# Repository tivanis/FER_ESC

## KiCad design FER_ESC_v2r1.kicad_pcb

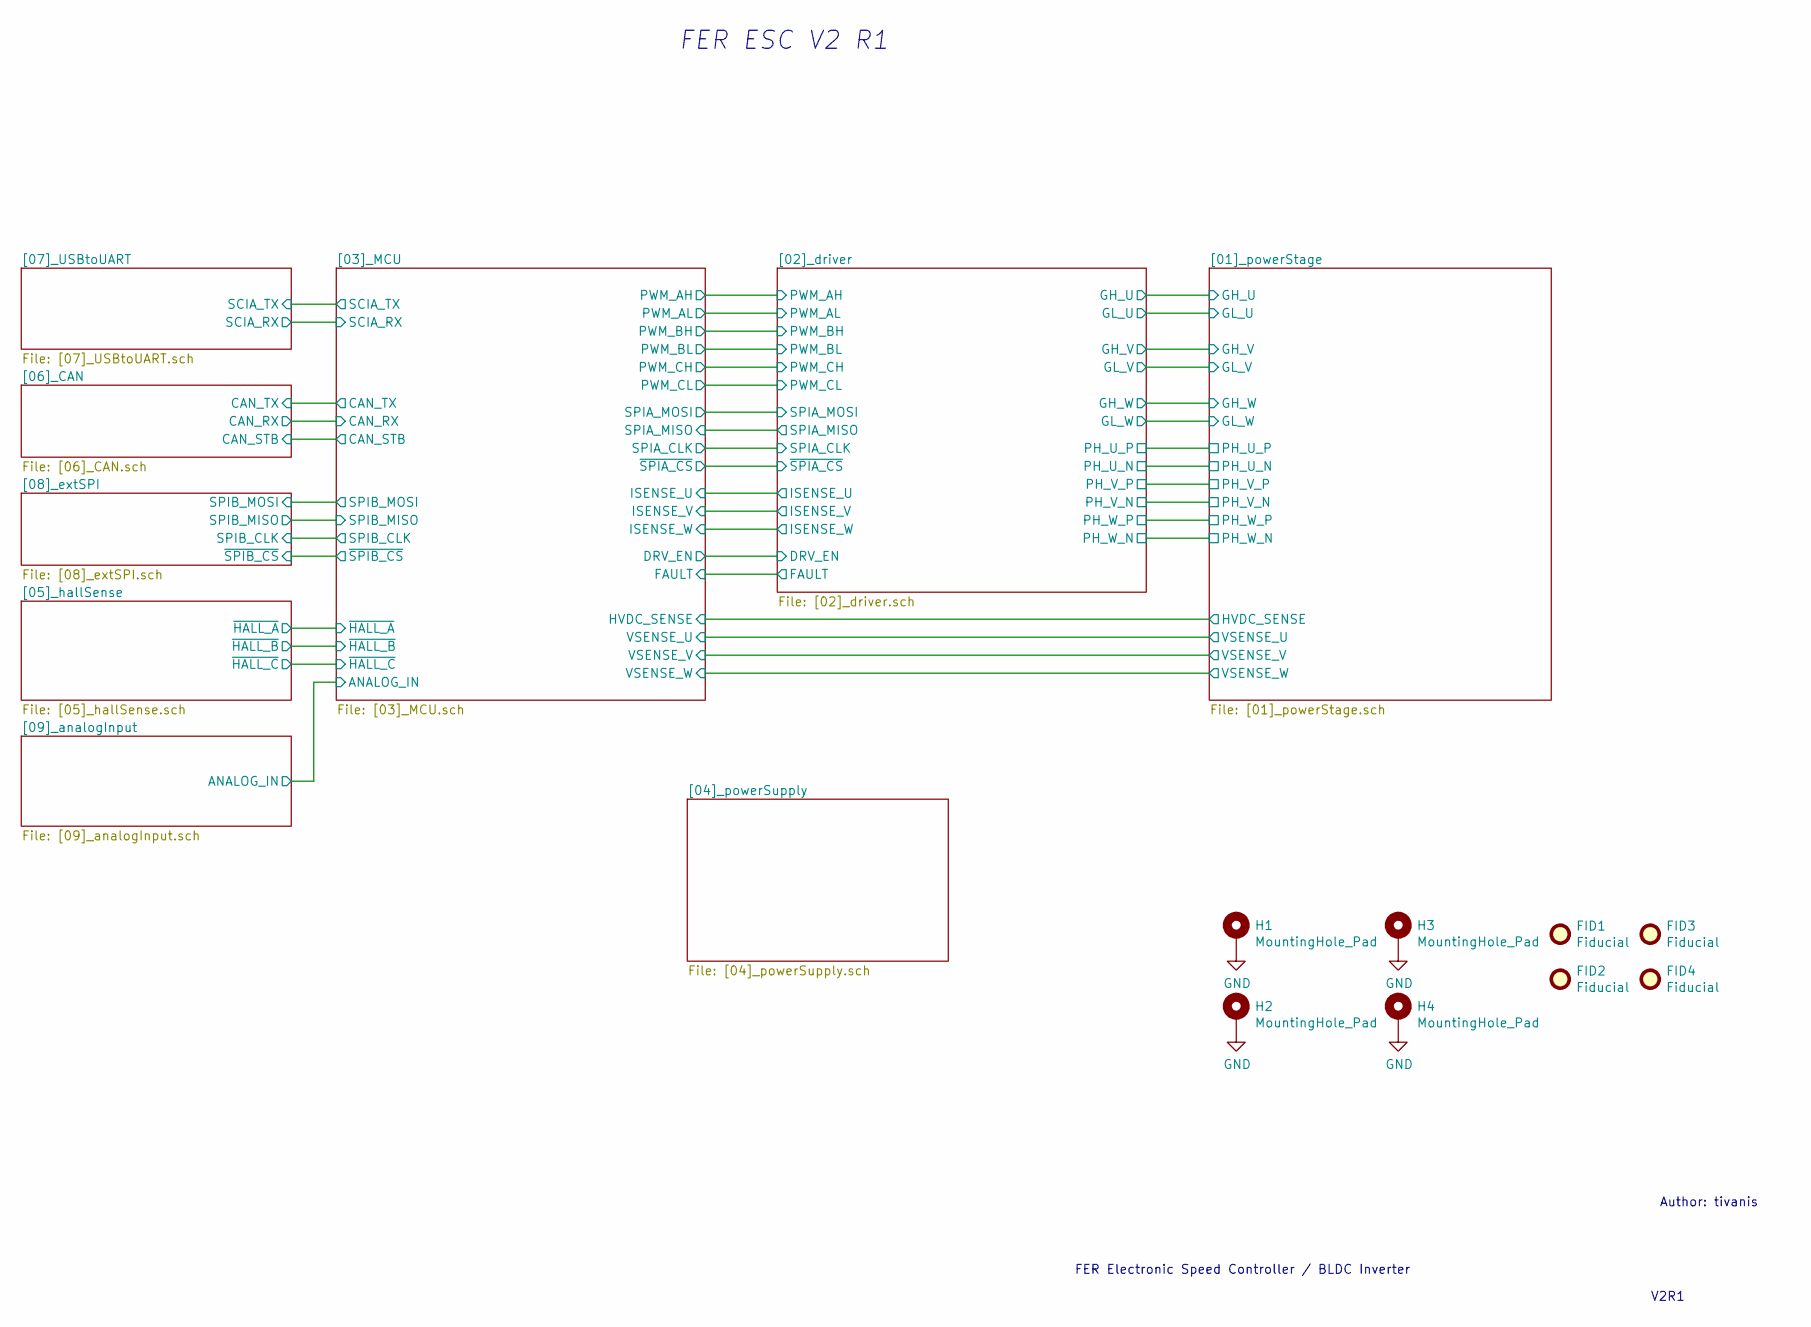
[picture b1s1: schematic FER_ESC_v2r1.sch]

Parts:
FID1, FID2, FID3, FID4: Fiducial; Fiducial_0.5mm_Mask1.5mm
H1, H2, H3, H4: MountingHole_Pad; MountingHole_3.2mm_M3_DIN965_Pad

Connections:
GND: H1.1, H2.1, H3.1, H4.1; also elsewhere on the board

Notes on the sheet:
FER ESC V2 R1
V2R1
FER Electronic Speed Controller / BLDC Inverter
Author: tivanis

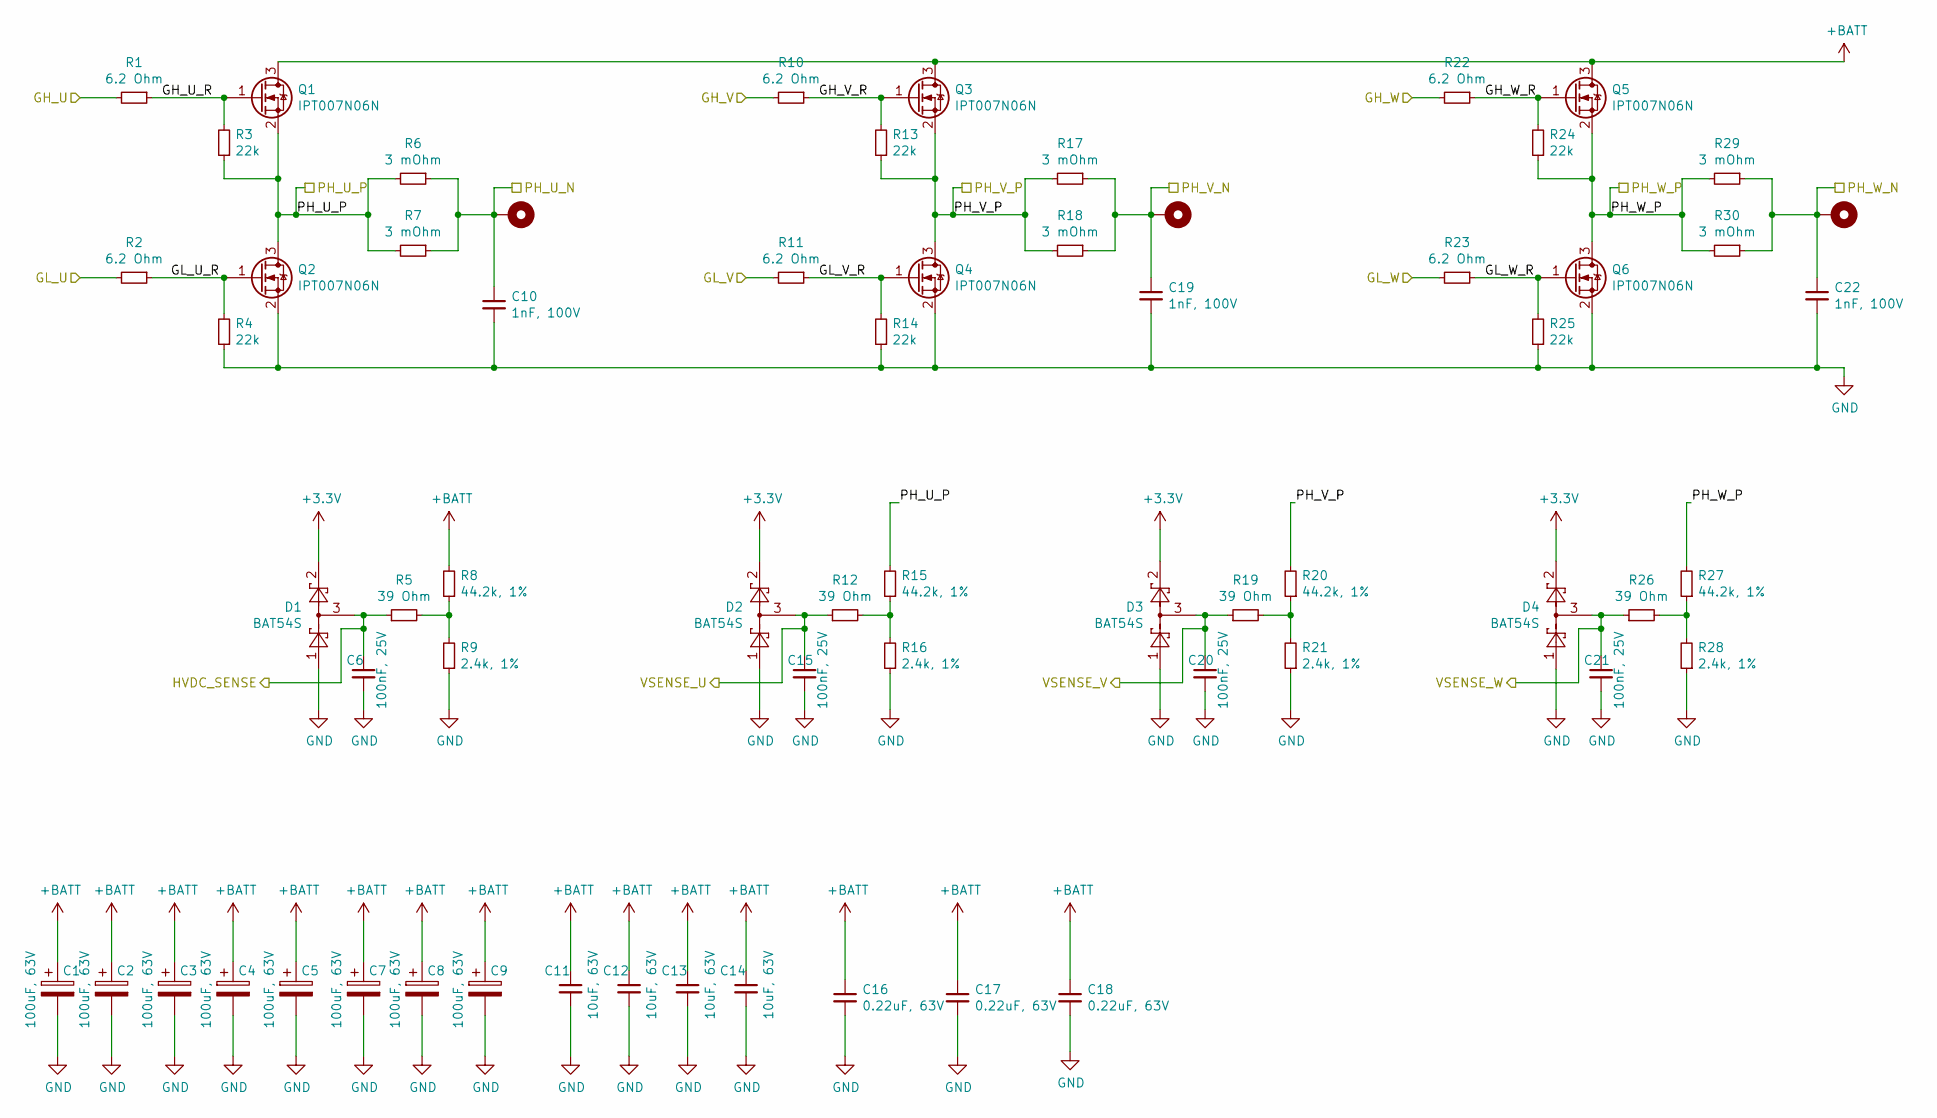
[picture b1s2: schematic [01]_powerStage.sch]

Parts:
C1, C2, C3, C4, C5, C7, C8, C9: 100uF, 63V; CP_Elec_10x14.3; Manufacturer Part Number EEH-ZS1J151V
C6, C15, C20, C21: 100nF, 25V; C_0603_1608Metric; Manufacturer Part Number C0603C104Z3VACTU
C10, C19, C22: 1nF, 100V; C_0603_1608Metric; Manufacturer Part Number C0603C102K1RACTU
C11, C12, C13, C14: 10uF, 63V; C_1210_3225Metric; Manufacturer Part Number CL32B106KMVNNWE
C16, C17, C18: 0.22uF, 63V; C_1206_3216Metric; Manufacturer Part Number C1206C224MMRECTU
D1, D2, D3, D4: BAT54S; SOT-23; Manufacturer Part Number BAT54S-TP
H5, H6, H7: MountingHole_Pad; MountingHole_4mm_Pad_Via
Q1, Q2, Q3, Q4, Q5, Q6: IPT007N06N; Infineon_PG-HSOF-8-1_ThermalVias; Manufacturer Part Number NVBLS001N06C
R1, R2, R10, R11, R22, R23: 6.2 Ohm; R_0805_2012Metric; Manufacturer Part Number ERJ-P06J6R2V
R3, R4, R13, R14, R24, R25: 22k; R_0805_2012Metric; Manufacturer Part Number ERJ-PA3J223V
R5, R12, R19, R26: 39 Ohm; R_0603_1608Metric; Manufacturer Part Number CR0603-FX-39R0ELF
R6, R7, R17, R18, R29, R30: 3 mOhm; R_2512_6332Metric; Manufacturer Part Number CSS2H-2512K-3L00FE
R8, R15, R20, R27: 44.2k, 1%; R_0603_1608Metric; Manufacturer Part Number CR0603-FX-4422ELF
R9, R16, R21, R28: 2.4k, 1%; R_0603_1608Metric; Manufacturer Part Number CR0603-FX-2401ELF

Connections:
+BATT: C1.1, C2.1, C3.1, C4.1, C5.1, C7.1, C8.1, C9.1, C11.1, C12.1, C13.1, C14.1, C16.1, C17.1, C18.1, Q1.3 (D), Q3.3 (D), Q5.3 (D), R8.2; also elsewhere on the board
/[01]_powerStage/GH_U: R1.2; also elsewhere on the board
/[01]_powerStage/GH_U_R: Q1.1 (G), R1.1, R3.2
/[01]_powerStage/GH_V: R10.2; also elsewhere on the board
/[01]_powerStage/GH_V_R: Q3.1 (G), R10.1, R13.2
/[01]_powerStage/GH_W: R22.2; also elsewhere on the board
/[01]_powerStage/GH_W_R: Q5.1 (G), R22.1, R24.2
/[01]_powerStage/GL_U: R2.2; also elsewhere on the board
/[01]_powerStage/GL_U_R: Q2.1 (G), R2.1, R4.2
/[01]_powerStage/GL_V: R11.2; also elsewhere on the board
/[01]_powerStage/GL_V_R: Q4.1 (G), R11.1, R14.2
/[01]_powerStage/GL_W: R23.2; also elsewhere on the board
/[01]_powerStage/GL_W_R: Q6.1 (G), R23.1, R25.2
/[01]_powerStage/HVDC_SENSE: C6.1, D1.3, R5.1; also elsewhere on the board
/[01]_powerStage/PH_U_N: C10.1, H5.1, R6.1, R7.1; also elsewhere on the board
/[01]_powerStage/PH_U_P: Q1.2 (S), Q2.3 (D), R3.1, R6.2, R7.2, R15.2; also elsewhere on the board
/[01]_powerStage/PH_V_N: C19.1, H6.1, R17.1, R18.1; also elsewhere on the board
/[01]_powerStage/PH_V_P: Q3.2 (S), Q4.3 (D), R13.1, R17.2, R18.2, R20.2; also elsewhere on the board
/[01]_powerStage/PH_W_N: C22.1, H7.1, R29.1, R30.1; also elsewhere on the board
/[01]_powerStage/PH_W_P: Q5.2 (S), Q6.3 (D), R24.1, R27.2, R29.2, R30.2; also elsewhere on the board
/[01]_powerStage/VSENSE_U: C15.1, D2.3, R12.1; also elsewhere on the board
/[01]_powerStage/VSENSE_V: C20.1, D3.3, R19.1; also elsewhere on the board
/[01]_powerStage/VSENSE_W: C21.1, D4.3, R26.1; also elsewhere on the board
GND: C1.2, C2.2, C3.2, C4.2, C5.2, C6.2, C7.2, C8.2, C9.2, C10.2, C11.2, C12.2, C13.2, C14.2, C15.2, C16.2, C17.2, C18.2, C19.2, C20.2, C21.2, C22.2, D1.1, D2.1, D3.1, D4.1, Q2.2 (S), Q4.2 (S), Q6.2 (S), R4.1, R9.1, R14.1, R16.1, R21.1, R25.1, R28.1; also elsewhere on the board
unnamed: R5.2, R8.1, R9.2
unnamed: R12.2, R15.1, R16.2
unnamed: R19.2, R20.1, R21.2
unnamed: R26.2, R27.1, R28.2

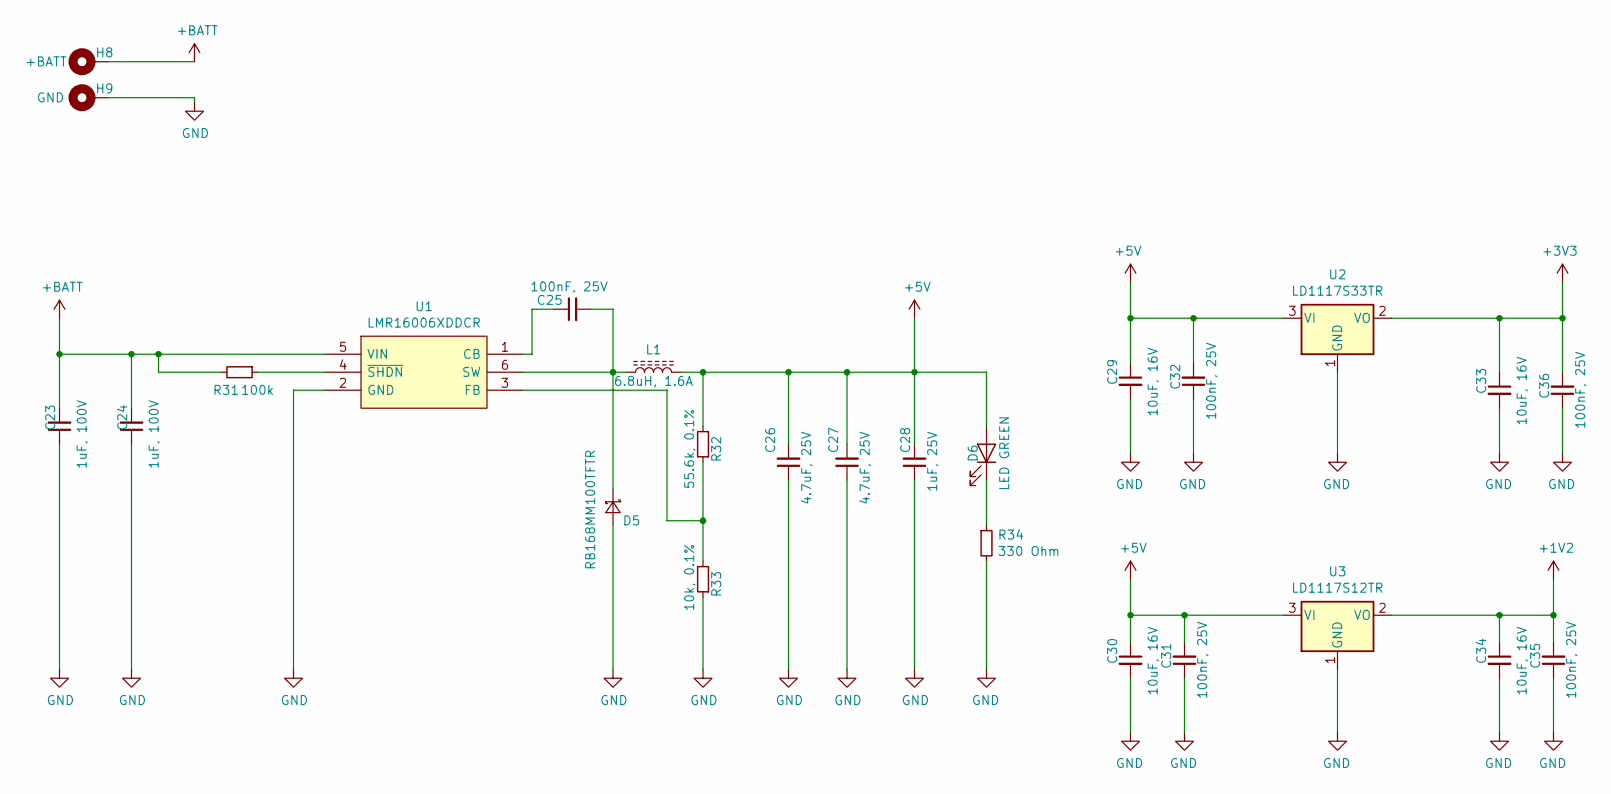
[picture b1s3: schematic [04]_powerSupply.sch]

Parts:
C23, C24: 1uF, 100V; C_0805_2012Metric; Mouser Part Number 81-GRM21BC72A105KE1L
C25, C31, C32, C35, C36: 100nF, 25V; C_0603_1608Metric; Manufacturer Part Number C0603C104Z3VACTU
C26, C27: 4.7uF, 25V; C_0805_2012Metric; Manufacturer Part Number 885012107018
C28: 1uF, 25V; C_0805_2012Metric; Mouser Part Number 603-CC805ZRY5V8BB105
C29, C30, C33, C34: 10uF, 16V; C_0805_2012Metric; Manufacturer Part Number EMK212BBJ106MGHT
D5: RB168MM100TFTR; D_SOD-123; Mouser Part Number 755-RB168MM100TFTR
D6: LED GREEN; LED_0603_1608Metric_Castellated; Manufacturer Part Number 155060VS75300
H8: +BATT; MountingHole_4mm_Pad_Via
H9: GND; MountingHole_4mm_Pad_Via
L1: 6.8uH, 1.6A; L_Taiyo-Yuden_NR-40xx_HandSoldering_ALT; Manufacturer Part Number TYS40306R8M-10
R31: 100k; R_0603_1608Metric; Manufacturer Part Number CR0603-FX-1003ELF
R32: 55.6k, 0.1%; R_0603_1608Metric; Manufacturer Part Number RN731JTTD5562B25
R33: 10k, 0.1%; R_0603_1608Metric; Manufacturer Part Number ERA-3AEB103V
R34: 330 Ohm; R_0603_1608Metric; Manufacturer Part Number CR0603-FX-3300ELF
U1: LMR16006XDDCR; TSOT-23-6; Manufacturer Part Number LMR16006XDDCR
U2: LD1117S33TR; SOT-223-3_TabPin2; Manufacturer Part Number LD1117S33TR
U3: LD1117S12TR; SOT-223-3_TabPin2; Manufacturer Part Number LD1117S12TR

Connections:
+1V2: C34.1, C35.2, U3.2 (VO); also elsewhere on the board
+5V: C26.2, C27.2, C28.2, C29.1, C30.1, C31.2, C32.2, D6.2 (A), L1.2, R32.2, U2.3 (VI), U3.3 (VI); also elsewhere on the board
+BATT: C23.2, C24.2, H8.1, R31.2, U1.5 (VIN); also elsewhere on the board
GND: C23.1, C24.1, C26.1, C27.1, C28.1, C29.2, C30.2, C31.1, C32.1, C33.2, C34.2, C35.1, C36.1, D5.2 (A), H9.1, R33.1, R34.2, U1.2 (GND), U2.1 (GND), U3.1 (GND); also elsewhere on the board
unnamed: C25.1, U1.1 (CB)
unnamed: C25.2, D5.1 (K), L1.1, U1.6 (SW)
unnamed: D6.1 (K), R34.1
unnamed: R31.1, U1.4 (~SHDN)
unnamed: R32.1, R33.2, U1.3 (FB)

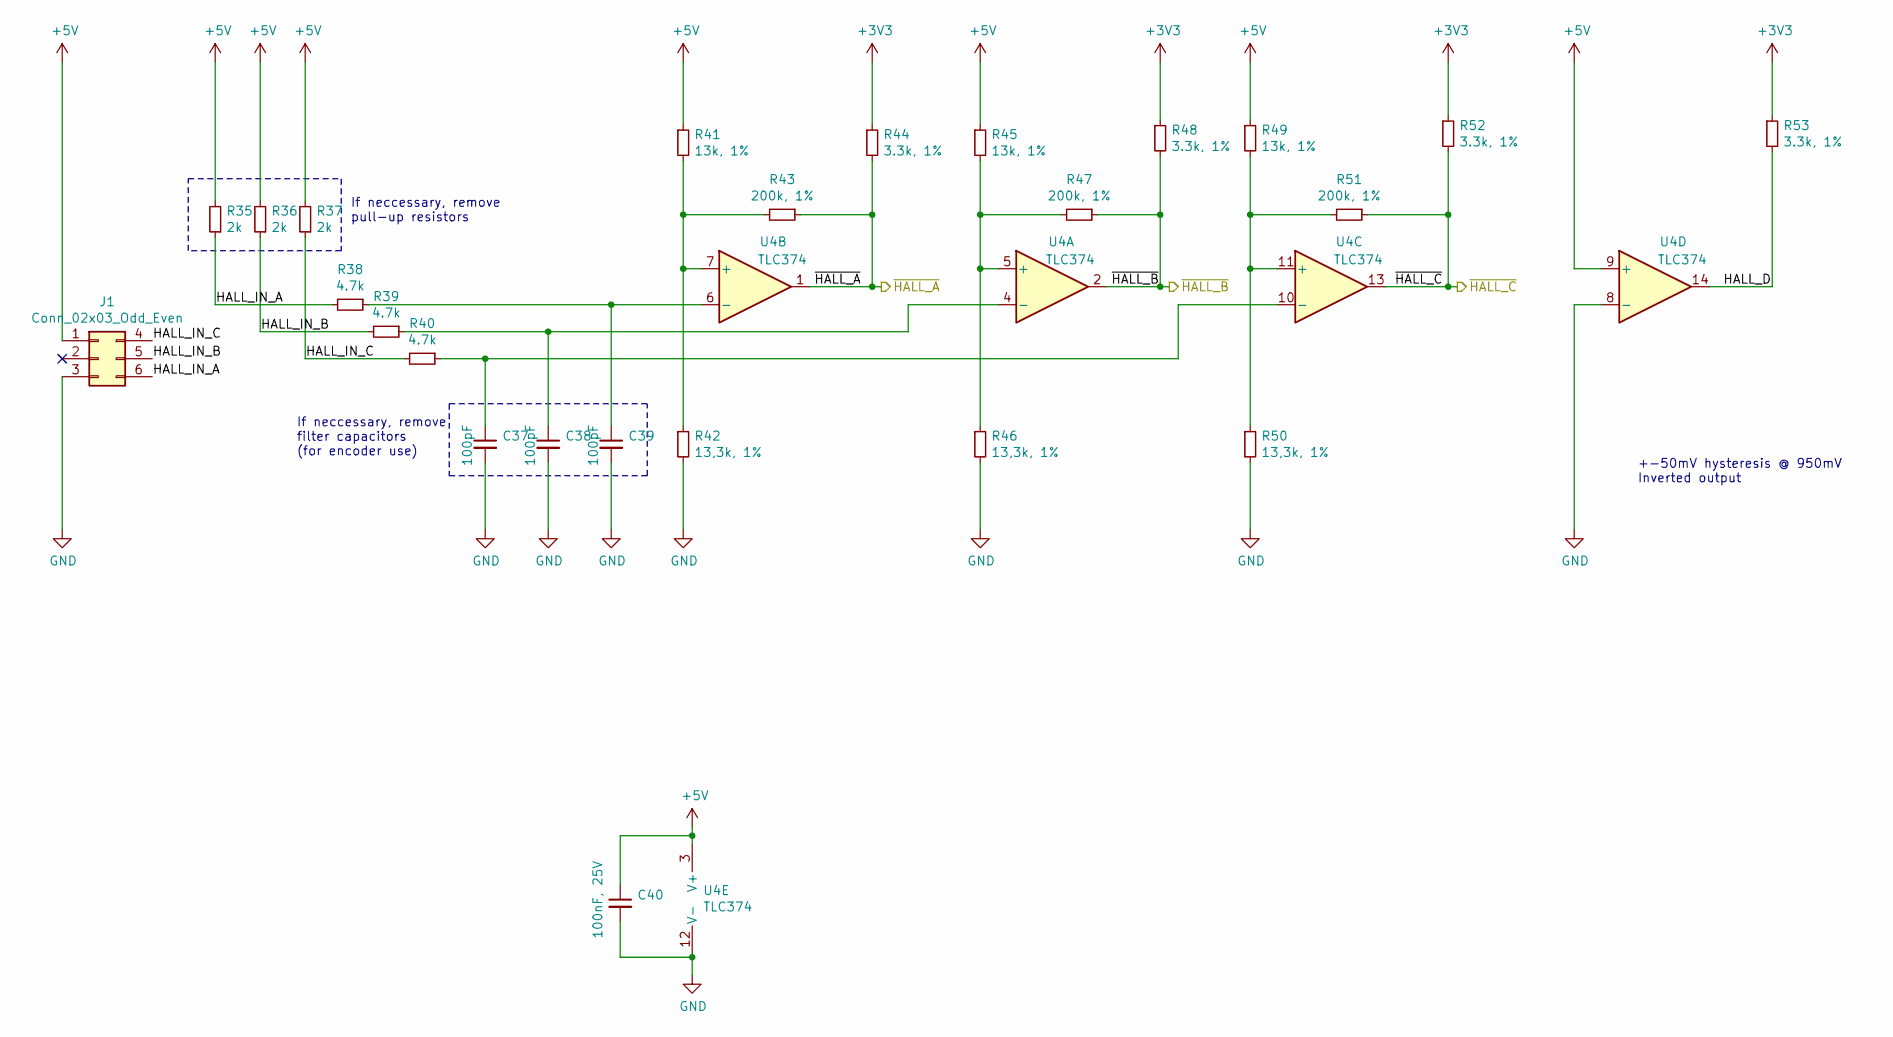
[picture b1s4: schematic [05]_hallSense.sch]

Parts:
C37, C38, C39: 100pF; C_0603_1608Metric; Manufacturer Part Number 885012206077
C40: 100nF, 25V; C_0603_1608Metric; Manufacturer Part Number C0603C104Z3VACTU
J1: Conn_02x03_Odd_Even; Molex_Nano-Fit_105314-xx06_2x03_P2.50mm_Horizontal; Manufacturer Part Number 105314-1206
R35, R36, R37: 2k; R_0603_1608Metric; Manufacturer Part Number CR0603-FX-2001ELF
R38, R39, R40: 4.7k; R_0603_1608Metric; Manufacturer Part Number CR0603-FX-4701ELF
R41, R45, R49: 13k, 1%; R_0603_1608Metric; Manufacturer Part Number CR0603-FX-1302ELF
R42, R46, R50: 13,3k, 1%; R_0603_1608Metric; Manufacturer Part Number CR0603-FX-1332ELF
R43, R47, R51: 200k, 1%; R_0603_1608Metric; Manufacturer Part Number CR0603-FX-2003ELF
R44, R48, R52, R53: 3.3k, 1%; R_0603_1608Metric; Manufacturer Part Number CR0603-FX-3301ELF
U4: TLC374; SOIC-14_3.9x8.7mm_P1.27mm; Manufacturer Part Number TLC374CDR

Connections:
+5V: C40.1, J1.1, R35.2, R36.2, R37.2, R41.1, R45.1, R49.1, U4.3 (V+), U4.9 (+); also elsewhere on the board
/[03]_MCU/~HALL_A: R43.1, R44.2, U4.1; also elsewhere on the board
/[03]_MCU/~HALL_B: R47.1, R48.2, U4.2; also elsewhere on the board
/[03]_MCU/~HALL_C: R51.1, R52.2, U4.13; also elsewhere on the board
/[05]_hallSense/HALL_D: R53.2, U4.14
/[05]_hallSense/HALL_IN_A: J1.6, R35.1, R38.2
/[05]_hallSense/HALL_IN_B: J1.5, R36.1, R39.2
/[05]_hallSense/HALL_IN_C: J1.4, R37.1, R40.2
GND: C37.2, C38.2, C39.2, C40.2, J1.3, R42.2, R46.2, R50.2, U4.8 (-), U4.12 (V-); also elsewhere on the board
unnamed: C37.1, R40.1, U4.10 (-)
unnamed: C38.1, R39.1, U4.4 (-)
unnamed: C39.1, R38.1, U4.6 (-)
unnamed: R41.2, R42.1, R43.2, U4.7 (+)
unnamed: R45.2, R46.1, R47.2, U4.5 (+)
unnamed: R49.2, R50.1, R51.2, U4.11 (+)

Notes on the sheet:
If neccessary, remove pull-up resistors
If neccessary, remove filter capacitors (for encoder use)
+-50mV hysteresis @ 950mV Inverted output

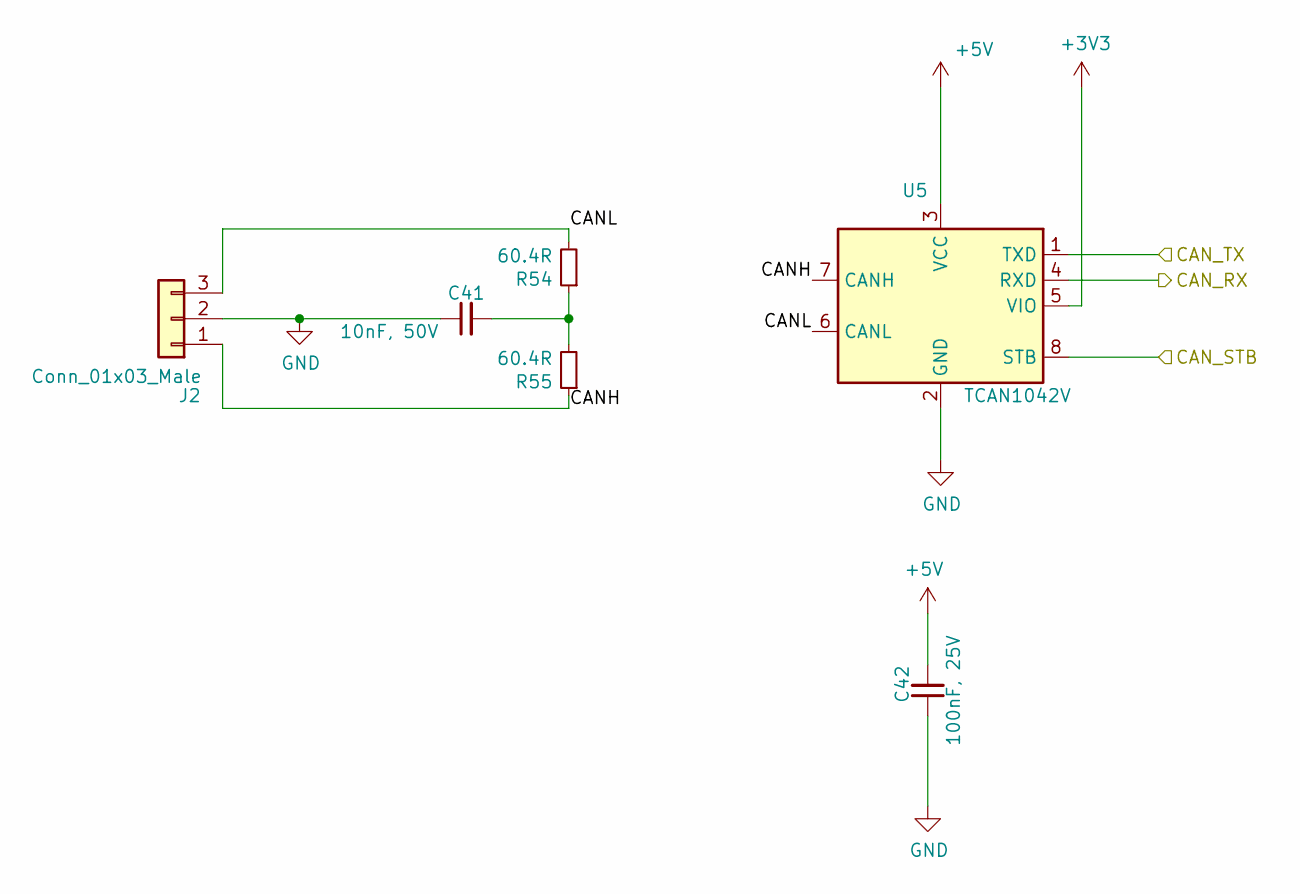
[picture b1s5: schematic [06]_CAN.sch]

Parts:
C41: 10nF, 50V; C_0603_1608Metric; Manufacturer Part Number 885012206089
C42: 100nF, 25V; C_0603_1608Metric; Manufacturer Part Number C0603C104Z3VACTU
J2: Conn_01x03_Male; Molex_Nano-Fit_105313-xx03_1x03_P2.50mm_Horizontal; Manufacturer Part Number 105313-1203
R54, R55: 60.4R; R_0603_1608Metric; Manufacturer Part Number ERJ-3EKF60R4V
U5: TCAN1042V; SOIC-8_3.9x4.9mm_P1.27mm; Manufacturer Part Number TCAN1042VDRQ1

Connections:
+5V: C42.2, U5.3 (VCC); also elsewhere on the board
/[03]_MCU/CAN_RX: U5.4 (RXD); also elsewhere on the board
/[03]_MCU/CAN_STB: U5.8 (STB); also elsewhere on the board
/[03]_MCU/CAN_TX: U5.1 (TXD); also elsewhere on the board
/[06]_CAN/CANH: J2.1, R55.1, U5.7 (CANH)
/[06]_CAN/CANL: J2.3, R54.2, U5.6 (CANL)
GND: C41.1, C42.1, J2.2, U5.2 (GND); also elsewhere on the board
unnamed: C41.2, R54.1, R55.2

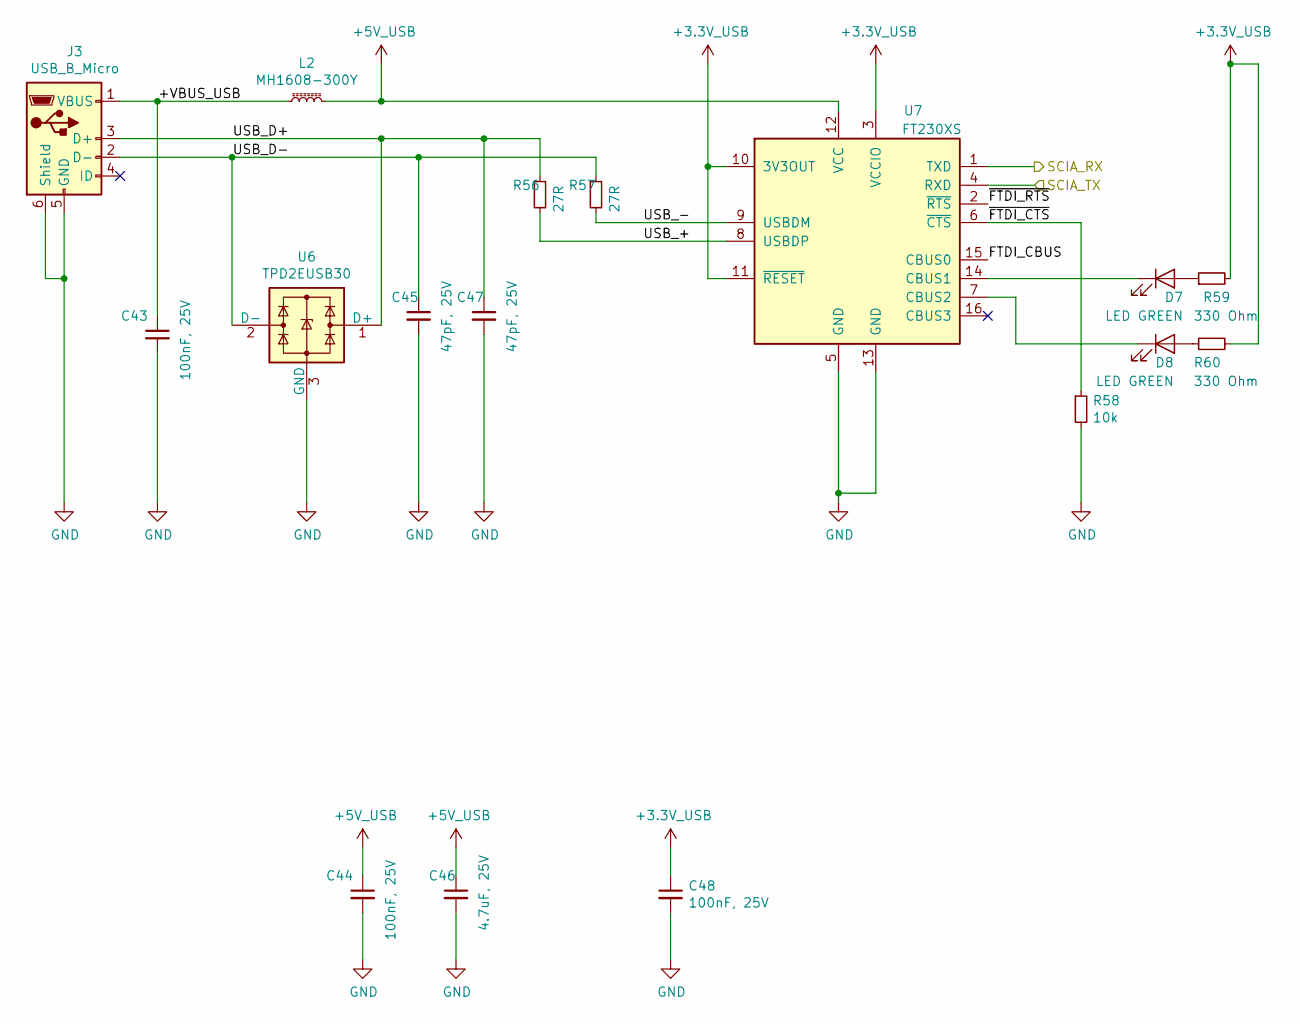
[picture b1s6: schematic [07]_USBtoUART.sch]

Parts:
C43, C44, C48: 100nF, 25V; C_0603_1608Metric; Manufacturer Part Number C0603C104Z3VACTU
C45, C47: 47pF, 25V; C_0603_1608Metric; Manufacturer Part Number VJ0603A470JXXPW1BC
C46: 4.7uF, 25V; C_0805_2012Metric; Manufacturer Part Number 885012107018
D7, D8: LED GREEN; LED_0603_1608Metric_Castellated; Manufacturer Part Number 155060VS75300
J3: USB_B_Micro; USB_Micro-B_Amphenol_10103594-0001LF_Horizontal; Manufacturer Part Number 10103594-0001LF
L2: MH1608-300Y; L_0603_1608Metric; Manufacturer Part Number MH1608-300Y
R56, R57: 27R; R_0603_1608Metric; Manufacturer Part Number CR0603-FX-27R0ELF
R58: 10k; R_0603_1608Metric; Manufacturer Part Number CR0603-FX-1002ELF
R59, R60: 330 Ohm; R_0603_1608Metric; Manufacturer Part Number CR0603-FX-3300ELF
U6: TPD2EUSB30; Texas_DRT-3; Manufacturer Part Number TPD2EUSB30
U7: FT230XS; SSOP-16_3.9x4.9mm_P0.635mm; Manufacturer Part Number FT230XS-R

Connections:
+3.3V_USB: C48.1, R59.2, R60.2, U7.3 (VCCIO), U7.10 (3V3OUT), U7.11 (~RESET)
+5V_USB: C44.1, C46.1, L2.2, U7.12 (VCC)
/[03]_MCU/SCIA_RX: U7.1 (TXD); also elsewhere on the board
/[03]_MCU/SCIA_TX: U7.4 (RXD); also elsewhere on the board
/[07]_USBtoUART/+VBUS_USB: C43.1, J3.1 (VBUS), L2.1
/[07]_USBtoUART/FTDI_CBUS: U7.15 (CBUS0)
/[07]_USBtoUART/USB_+: R56.1, U7.8 (USBDP)
/[07]_USBtoUART/USB_-: R57.1, U7.9 (USBDM)
/[07]_USBtoUART/USB_D+: C47.1, J3.3 (D+), R56.2, U6.1 (D+)
/[07]_USBtoUART/USB_D-: C45.1, J3.2 (D-), R57.2, U6.2 (D-)
/[07]_USBtoUART/~FTDI_CTS: R58.1, U7.6 (~CTS)
/[07]_USBtoUART/~FTDI_RTS: U7.2 (~RTS)
GND: C43.2, C44.2, C45.2, C46.2, C47.2, C48.2, J3.5 (GND), J3.6 (Shield), R58.2, U6.3 (GND), U7.5 (GND), U7.13 (GND); also elsewhere on the board
unnamed: D7.1 (K), U7.14 (CBUS1)
unnamed: D7.2 (A), R59.1
unnamed: D8.1 (K), U7.7 (CBUS2)
unnamed: D8.2 (A), R60.1

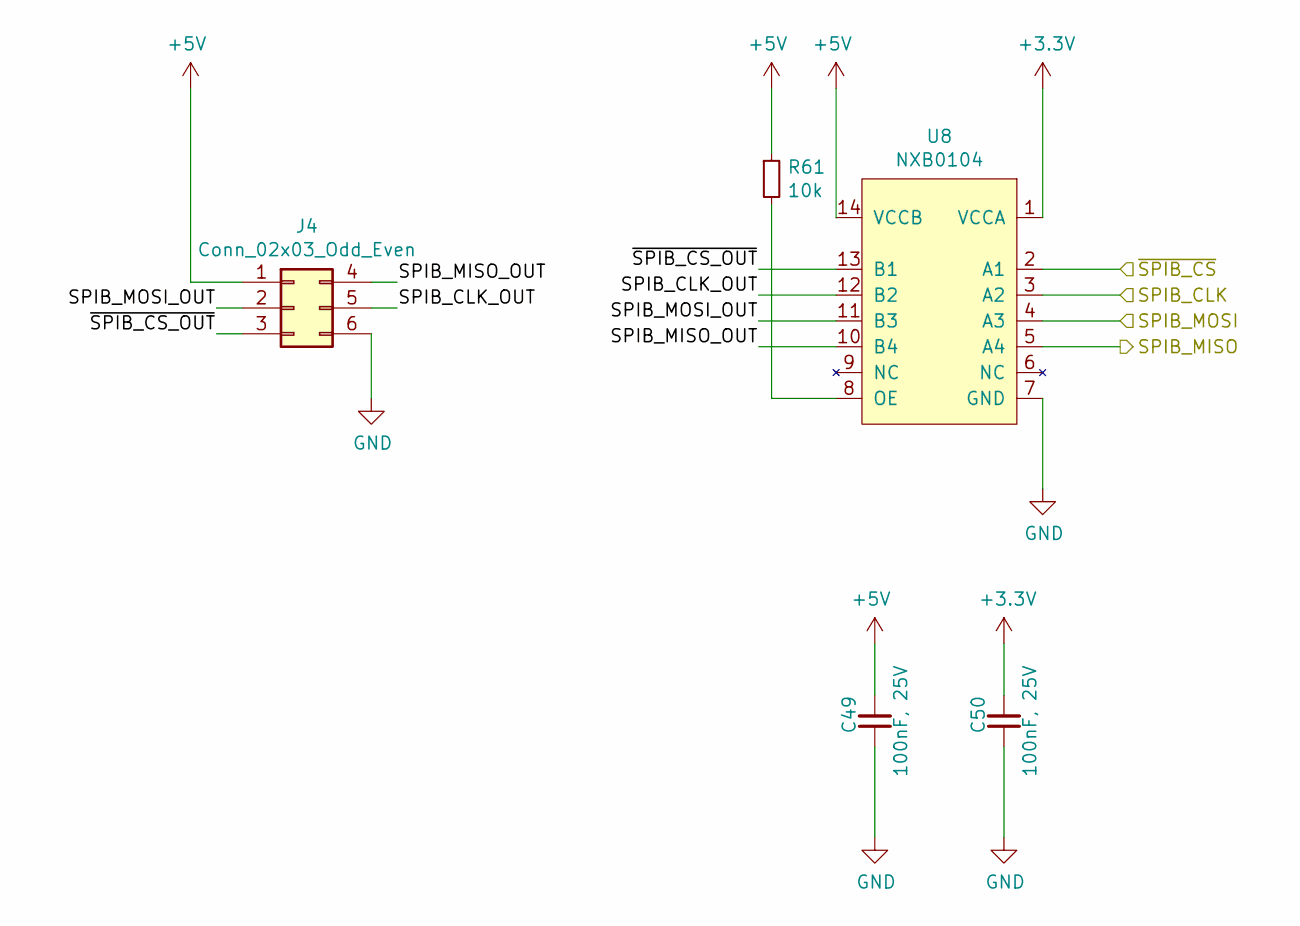
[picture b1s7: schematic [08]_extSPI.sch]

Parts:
C49, C50: 100nF, 25V; C_0603_1608Metric; Manufacturer Part Number C0603C104Z3VACTU
J4: Conn_02x03_Odd_Even; Molex_Nano-Fit_105314-xx06_2x03_P2.50mm_Horizontal; Manufacturer Part Number 105314-1206
R61: 10k; R_0603_1608Metric; Manufacturer Part Number CR0603-FX-1002ELF
U8: NXB0104; TSSOP-14_4.4x5mm_P0.65mm; Manufacturer Part Number NXS0104PW-Q100J

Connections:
+5V: C49.2, J4.1, R61.1, U8.14 (VCCB); also elsewhere on the board
/[03]_MCU/SPIB_CLK: U8.3 (A2); also elsewhere on the board
/[03]_MCU/SPIB_MISO: U8.5 (A4); also elsewhere on the board
/[03]_MCU/SPIB_MOSI: U8.4 (A3); also elsewhere on the board
/[03]_MCU/~SPIB_CS: U8.2 (A1); also elsewhere on the board
/[08]_extSPI/SPIB_CLK_OUT: J4.5, U8.12 (B2)
/[08]_extSPI/SPIB_MISO_OUT: J4.4, U8.10 (B4)
/[08]_extSPI/SPIB_MOSI_OUT: J4.2, U8.11 (B3)
/[08]_extSPI/~SPIB_CS_OUT: J4.3, U8.13 (B1)
GND: C49.1, C50.1, J4.6, U8.7 (GND); also elsewhere on the board
unnamed: R61.2, U8.8 (OE)

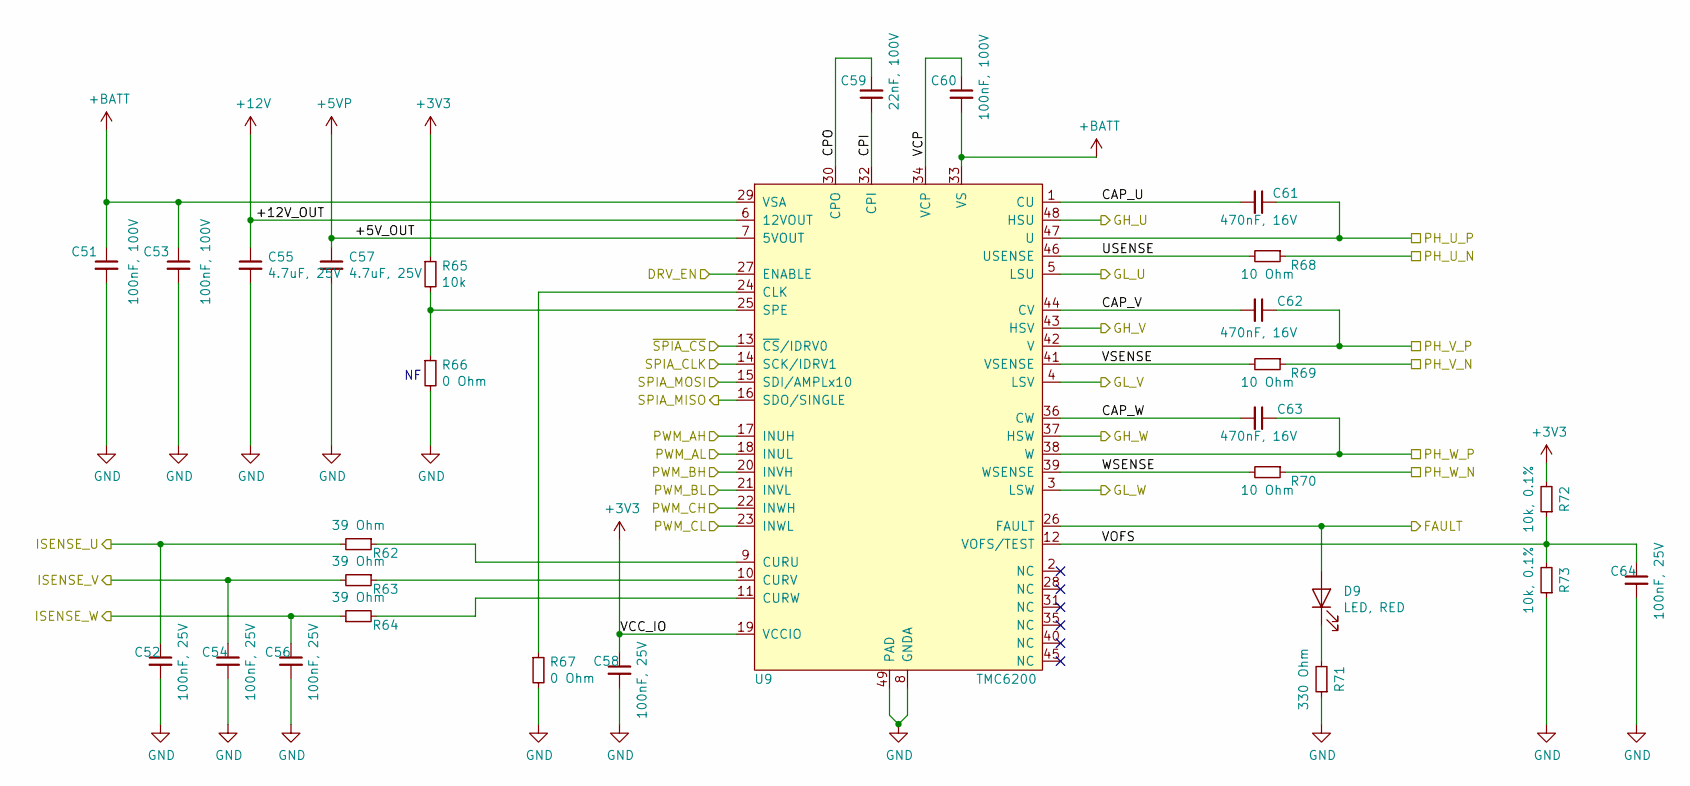
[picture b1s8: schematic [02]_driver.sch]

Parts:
C51, C53, C60: 100nF, 100V; C_0805_2012Metric; Manufacturer Part Number 885012207128
C52, C54, C56, C58, C64: 100nF, 25V; C_0603_1608Metric; Manufacturer Part Number C0603C104Z3VACTU
C55, C57: 4.7uF, 25V; C_0805_2012Metric; Manufacturer Part Number 885012107018
C59: 22nF, 100V; C_0603_1608Metric; Manufacturer Part Number C0603C223K1RACTU
C61, C62, C63: 470nF, 16V; C_0603_1608Metric; Manufacturer Part Number CC0603JRX7R7BB474
D9: LED, RED; LED_0603_1608Metric_Castellated; Manufacturer Part Number 150060RS75000
R62, R63, R64: 39 Ohm; R_0603_1608Metric; Manufacturer Part Number CR0603-FX-39R0ELF
R65: 10k; R_0603_1608Metric; Manufacturer Part Number CR0603-FX-1002ELF
R66, R67: 0 Ohm; R_0603_1608Metric; Manufacturer Part Number AC0603JR-100RL
R68, R69, R70: 10 Ohm; R_0603_1608Metric; Manufacturer Part Number CR0603AFX-10R0EAS
R71: 330 Ohm; R_0603_1608Metric; Manufacturer Part Number CR0603-FX-3300ELF
R72, R73: 10k, 0.1%; R_0603_1608Metric; Manufacturer Part Number ERA-3AEB103V
U9: TMC6200; TQFP-48-1EP_7x7mm_P0.5mm_EP5x5mm_ThermalVias; Manufacturer Part Number TMC6200

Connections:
+5VP: C57.1, U9.7 (5VOUT)
+12V: C55.1, U9.6 (12VOUT)
+BATT: C51.1, C53.1, C60.2, U9.29 (VSA), U9.33 (VS); also elsewhere on the board
/[01]_powerStage/GH_U: U9.48 (HSU); also elsewhere on the board
/[01]_powerStage/GH_V: U9.43 (HSV); also elsewhere on the board
/[01]_powerStage/GH_W: U9.37 (HSW); also elsewhere on the board
/[01]_powerStage/GL_U: U9.5 (LSU); also elsewhere on the board
/[01]_powerStage/GL_V: U9.4 (LSV); also elsewhere on the board
/[01]_powerStage/GL_W: U9.3 (LSW); also elsewhere on the board
/[01]_powerStage/PH_U_N: R68.1; also elsewhere on the board
/[01]_powerStage/PH_U_P: C61.1, U9.47 (U); also elsewhere on the board
/[01]_powerStage/PH_V_N: R69.1; also elsewhere on the board
/[01]_powerStage/PH_V_P: C62.1, U9.42 (V); also elsewhere on the board
/[01]_powerStage/PH_W_N: R70.1; also elsewhere on the board
/[01]_powerStage/PH_W_P: C63.1, U9.38 (W); also elsewhere on the board
/[02]_driver/CAP_U: C61.2, U9.1 (CU)
/[02]_driver/CAP_V: C62.2, U9.44 (CV)
/[02]_driver/CAP_W: C63.2, U9.36 (CW)
/[02]_driver/CPI: C59.1, U9.32 (CPI)
/[02]_driver/CPO: C59.2, U9.30 (CPO)
/[02]_driver/DRV_EN: U9.27 (ENABLE); also elsewhere on the board
/[02]_driver/FAULT: D9.2 (A), U9.26 (FAULT); also elsewhere on the board
/[02]_driver/ISENSE_U: C52.1, R62.2; also elsewhere on the board
/[02]_driver/ISENSE_V: C54.1, R63.2; also elsewhere on the board
/[02]_driver/ISENSE_W: C56.1, R64.1; also elsewhere on the board
/[02]_driver/PWM_AH: U9.17 (INUH); also elsewhere on the board
/[02]_driver/PWM_AL: U9.18 (INUL); also elsewhere on the board
/[02]_driver/PWM_BH: U9.20 (INVH); also elsewhere on the board
/[02]_driver/PWM_BL: U9.21 (INVL); also elsewhere on the board
/[02]_driver/PWM_CH: U9.22 (INWH); also elsewhere on the board
/[02]_driver/PWM_CL: U9.23 (INWL); also elsewhere on the board
/[02]_driver/SPIA_CLK: U9.14 (SCK/IDRV1); also elsewhere on the board
/[02]_driver/SPIA_MISO: U9.16 (SDO/SINGLE); also elsewhere on the board
/[02]_driver/SPIA_MOSI: U9.15 (SDI/AMPLx10); also elsewhere on the board
/[02]_driver/USENSE: R68.2, U9.46 (USENSE)
/[02]_driver/VCP: C60.1, U9.34 (VCP)
/[02]_driver/VOFS: C64.1, R72.1, R73.2, U9.12 (VOFS/TEST)
/[02]_driver/VSENSE: R69.2, U9.41 (VSENSE)
/[02]_driver/WSENSE: R70.2, U9.39 (WSENSE)
/[02]_driver/~SPIA_CS: U9.13 (~CS~/IDRV0); also elsewhere on the board
GND: C51.2, C52.2, C53.2, C54.2, C55.2, C56.2, C57.2, C58.2, C64.2, R66.2, R67.2, R71.1, R73.1, U9.8 (GNDA), U9.49 (PAD); also elsewhere on the board
unnamed: D9.1 (K), R71.2
unnamed: R62.1, U9.9 (CURU)
unnamed: R63.1, U9.10 (CURV)
unnamed: R64.2, U9.11 (CURW)
unnamed: R65.2, R66.1, U9.25 (SPE)
unnamed: R67.1, U9.24 (CLK)

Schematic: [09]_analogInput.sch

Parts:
C86: 100nF, 25V; C_0603_1608Metric; Manufacturer Part Number C0603C104Z3VACTU
F1: Fuse_Small; Fuse_0603_1608Metric; Manufacturer Part Number F0603G0R15FNTR
J7: Conn_01x03_Male; Molex_Nano-Fit_105313-xx03_1x03_P2.50mm_Horizontal; Manufacturer Part Number 105313-1203
R84: 39 Ohm; R_0603_1608Metric; Manufacturer Part Number CR0603-FX-39R0ELF

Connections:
/[03]_MCU/ANALOG_IN: C86.1, R84.1; also elsewhere on the board
GND: C86.2, J7.1; also elsewhere on the board
unnamed: F1.1, J7.3
unnamed: J7.2, R84.2
